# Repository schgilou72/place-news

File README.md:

# place-news

KiCad action plugins for boards where **isolation matters** (switch-mode power
supplies, mains and high-voltage circuits):

- **place-news** — automatic component placement (simulated annealing) that
  keeps parts as far apart as your clearance and creepage rules demand, and
  honours KiCad rule areas (keep-outs, placement areas). Then a tidy-up: parts
  in rows and columns, readable references, and an untangled ratsnest (fewer
  vias).
- **place-news — Route (Freerouting)** — autorouting with
  [Freerouting](https://github.com/freerouting/freerouting), with your net-class
  clearances and custom `.kicad_dru` rules (clearance, creepage) passed to the
  router; fewer vias, a try on the two outer layers when the board has more,
  and a ground plane on the top layer that keeps the creepage distances.
- **place-news — Aesthetic check** — scores the look and the cost of the
  placement and routing, marks every issue on the board and in a visual
  report, estimates how many layers the board needs, and learns your taste
  from your opinion and from your own corrections.
- **place-news — Sourcing (BOM)** — stock, prices, minimum orders, lifecycle
  and replacements of every BOM line at DigiKey, Mouser, Farnell, TME and
  LCSC; the chosen parts written into the components' fields, a BOM with the
  designators, unit prices and minimum orders, and one order list per
  distributor.

KiCad's own DRC stays the judge: placement and routing can finish with a DRC run, and the
rules are always applied on the safe side (straight-line distance, never longer
than KiCad's creepage path).

place-news is derived from [CadMust-Neo](https://github.com/remiblokker/CadMust-Neo)
by Remi Blokker (MIT licence).

## Requirements

- KiCad 10.0 (tested with 10.0.6). Uses the SWIG Python API, which KiCad 10
  still ships (it is planned to be removed in KiCad 11).
- For routing: **Java 25 or later** and **Freerouting 2.4 or later**
  (`freerouting-2.x.x-executable.jar`, from the
  [Freerouting releases](https://github.com/freerouting/freerouting/releases)
  or installed by KiCad's Freerouting plugin). Java: e.g.
  [Eclipse Temurin](https://adoptium.net/temurin/releases/).
- For sourcing: an internet connection, and the free API keys of the
  distributors you use (LCSC needs none).
- Nothing else: pure Python, no extra packages.

## Installation

Download the archive from the
[Releases](https://github.com/schgilou72/place-news/releases) page.

**Plugin and Content Manager (recommended):** in KiCad, *Plugin and Content
Manager → Install from File…* and choose `place-news-<version>-pcm.zip`.

**Manual:** in the PCB editor, *Tools → External Plugins → Open Plugin
Directory*, unzip `place-news-<version>-plugin.zip` there (it holds the
`place_news/` folder), then *Tools → External Plugins → Refresh Plugins*.

Four toolbar buttons appear: placement (green grid), routing (trace with a
dashed isolation line), the aesthetic check (magnifier) and sourcing (cart).

To try it: open `examples/flyback/flyback.kicad_pcb` (an isolated flyback
with HV / PRI / SEC net classes and 6 mm creepage rules, parts still piled up)
and run the placement and the routing.

## Placement

1. Draw the board outline on Edge.Cuts; lock connectors, mounting holes and
   anything mechanically fixed.
2. Optional: rule areas with *Keep out footprints / pads* reserve space; rule
   areas with *Placement* enabled (sheet, component class or group) keep their
   parts inside — and, with *Exclusive placement areas*, other parts outside.
3. Click **place-news**, choose a preset, **Optimize**.
4. The result dialog lists wirelength, overlaps, isolation, placement areas,
   keep-outs, alignment, ratsnest crossings and silkscreen. *Reject* (or
   *Edit → Undo*) restores the previous placement.

### Tidy layout

- **Rows and columns** (*Align parts of the same type in rows / columns*, on by
  default): parts with the same footprint and orientation that sit roughly in
  a row or a column are put on one line through their centres, and lines of
  three or more are evenly spaced. A locked part of the same type serves as
  the anchor. A move is kept only if no rule gets worse (overlap, isolation,
  keep-outs, placement areas, board edge) and the wirelength grows by 3 % at
  most.
- **Readable references**: each reference is centred on its part, horizontal
  or vertical reading bottom to top (never upside down nor top to bottom),
  along the long side of the part. It never touches a pad or another
  reference: when pads take the centre, it goes beside the part, centred on
  its axis. References of locked parts are left alone.
- **Untangled ratsnest** (*Reduce cost: untangle the ratsnest*, on by
  default): every crossing of two ratsnest lines tends to cost a via. Identical
  parts swap places with their nearest twins and two-pad parts turn round
  (180°) when that removes crossings; rows, columns and orientation axes stay.
  Power nets are left out (they go to a plane or a pour). Same safeguards as
  above, 2 % of wirelength at most. On KiCad's demo boards, with their
  hand-made placements: complex_hierarchy 28 → 18 crossings, pic_programmer
  22 → 17.

### Isolation during placement

For every pair of pads on different nets, the required distance is the larger
of:

- the clearance KiCad applies: net-class clearance (the larger of the two), or
  the last matching custom `clearance` rule, never below the board minimum;
- `physical_clearance` rules;
- `creepage` rules. KiCad evaluates creepage **between nets** (with a stand-in
  track of each net on every copper layer), so creepage conditions can use net
  names, net classes and layers, not footprint properties.

Non-plated holes (mounting holes) count for creepage only. Pairs inside one
footprint cannot be fixed by placement; they are reported separately ("inside
footprints"), as are pairs between two locked parts.

### Supported rule conditions

`A.`/`B.` with `NetClass`, `NetName`, `Type`, `Pad_Type`, `Layer`,
`hasNetclass()`, `hasExactNetclass()`, `hasComponentClass()`,
`memberOfSheet()`, `memberOfSheetOrChildren()`, `memberOfFootprint()`
(reference, `lib:footprint` or `${Class:…}`), `memberOfGroup()`,
`existsOnLayer()`, `isPlated()`, combined with `!`, `&&`, `||`, `==`, `!=` and
parentheses. Semantics follow KiCad: last matching rule wins, a rule matches if
its condition holds for (A, B) or (B, A), `&&` binds less tightly than `||`,
string `==` is case-insensitive and accepts `*`/`?` in a right-hand literal.
A rule using anything else is listed as ignored in the dialogs — never guessed.

Example (`<project>.kicad_dru`):

```
(version 1)
(rule "isolation creepage"
  (constraint creepage (min 6mm))
  (condition "(A.hasNetclass('HV') || A.hasNetclass('PRI')) && B.hasNetclass('SEC')"))
(rule "isolation clearance"
  (constraint clearance (min 4mm))
  (condition "(A.hasNetclass('HV') || A.hasNetclass('PRI')) && B.hasNetclass('SEC')"))
```

## Routing with Freerouting

1. Place the parts (with place-news or by hand) and save the board.
2. Click **place-news — Route (Freerouting)**. The dialog finds the
   Freerouting jar and Java (or lets you pick them) and shows the isolation
   distances that will be given to the router.
3. Cost options: **Fewer vias** (Freerouting's via cost × 3; if that leaves
   connections unrouted, the board is routed again at the usual cost and the
   more complete result is kept) and, on boards with more than two copper
   layers, **Try the 2 outer layers first** (the inner layers become planes
   for Freerouting; if every connection is made, that result is kept and the
   summary says the inner layers can go, unless they are planes).
4. **Ground plane**: *Pour on the top layer (F.Cu)*, with the ground net
   (GND, PGND, 0V… found by name). See below.
5. **Route**. Freerouting runs in the background (progress, *Cancel*), the
   routes are imported, the pour is made, then KiCad's DRC runs on a copy of
   the board and the summary shows unrouted connections, vias, the routing
   room, the pour and the clearance / creepage results.
6. *Edit → Undo* reverts the routing and the pour.

What place-news changes in the Specctra file before routing:

- **Rule areas**: KiCad exports every rule area as a full routing keep-out,
  even areas that only keep out footprints or pads, and placement areas. Each
  area now follows its own *Keep out tracks / vias* settings.
- **Isolation rules**: Freerouting knows one clearance per pair of net
  classes. Each class gets the clearance its own nets need between them, and a
  `class_class` rule is written for every pair of classes that needs another
  value (e.g. 6 mm between primary and secondary classes). Creepage becomes a
  straight-line clearance.
- KiCad's `smd_smd` pad-to-pad allowance is dropped when it would let the
  default class bypass these rules; Freerouting may then report pad-to-pad
  "violations" inside fine-pitch footprints (pads are fixed; KiCad's DRC is
  what counts).
- Freerouting ≥ 2.4 may fan out SMD pins with the default class's vias when a
  class's own via does not fit; that is disabled, since those vias would carry
  the default clearance.
- Parts never move: the session's placement section is ignored on import.

Freerouting runs with `--usage_and_diagnostic_data.disable_analytics=true`.
It still checks GitHub for a newer version when it starts.

### Ground plane on the top layer

The chosen net is poured over the whole top layer (zones named
`place-news pour`; running again replaces them). KiCad's zone filler keeps
the clearances, but not the creepage distances — and a pour runs along the
board surface, the very path creepage is measured on. So every copper item on
the top layer whose required distance to the pour's net (clearance, physical
clearance or creepage, from the net classes and the custom rules) is larger
than the plain clearance is kept clear by that distance (+ 20 µm for the
fill's rounding). Each cluster of such items — a primary side, say — gets one
convex cut-out: a clean isolation boundary, no copper fingers between the
primary parts. Islands are removed; pads connect with thermal reliefs. On the
example flyback, KiCad's DRC finds no clearance, creepage or unconnected item
with the pour.

### Known KiCad behaviour

KiCad's creepage check treats rule areas as items without a net: with a rule
such as `A.hasNetclass('HV') && !B.hasNetclass('HV')`, it reports "creepage"
between HV pads and nearby rule-area outlines. Writing the rule against an
explicit class (`B.hasNetclass('SEC')`) avoids it. The route summary counts
these separately.

## Aesthetic check

**place-news — Aesthetic check** scores the board out of 100 in three groups
and numbers every issue on the *User.Comments* layer (one group, easy to
delete) and in an HTML report next to the board (`<board>-aesthetic-check.html`:
drawing of the board, markers, criteria, issues; hover a row to find its
marker).

- **Placement**: same-type parts aligned, one orientation per part type,
  references readable (0° / 90°), on their part or its axis, clear of pads.
- **Routing**: 45° steps, no acute angles, no small zigzags, no long detours
  (routed length against the shortest 45° tree), tracks leaving pads straight.
- **Cost**: few vias, untangled ratsnest, few drill sizes, no drill under
  0.3 mm, no track under 0.15 mm, parts on one side, no empty inner layer,
  layer count fitting the routing room, board not larger than needed.

**Learning.** The dialog asks what you think (👍 / 👎, and optionally what
bothers you most): the criteria you name gain weight. When you edit a board
place-news produced and run the check again, the criteria your edits improved
gain weight, those you let degrade lose some, and the knobs place-news turned
(tidy-up budgets, via cost) are rewarded or penalised by how much you had to
fix — a small evolution-strategies loop: each run tries the knobs a little
differently and keeps what you liked. Everything stays in
`place-news/place-news-aesthetics.json` in KiCad's settings folder.

### How many layers?

The routing room per net — the rule of thumb

    (board area × routing layers − parts area) / number of nets

— is compared with what an average net needs: its ratsnest length (45°
spanning tree, × 1.3 for detours) times its track pitch (net-class width +
clearance), over the share of free area tracks can really use (60 %). That is
Coors' "wiring demand / routing capacity per layer". Parts with pads in a grid
(BGA) also need layers to escape: rings of pads ÷ (tracks between pads + 1).
Inner layers used as planes are not routing room, and never a cost (power,
EMC). Fewer layers are suggested only with 30 % of room to spare.

Calibrated on the boards shipped with KiCad: the estimated track area matches
the routed one within about 10 %. Quick rules of thumb are shown next to it
for comparison; they ask for far too many layers on fine-pitch SMD boards:

| Board | Layers | Pin density (in² per 14 pins) | Parts / board | Pins per cm² | place-news |
|---|---|---|---|---|---|
| pic_programmer (through-hole) | 2 | 1.46 → 2 | 49 % | 1.5 | 2 fit |
| interf_u | 2 | 0.71 → 2 + planes | 52 % | 3.1 | 2 fit |
| sonde xilinx | 2 | 0.70 → 2 + planes | 80 % → "6–8" | 3.1 | 2 fit |
| StickHub (fine-pitch SMD) | 2 | 0.05 → 10 signal | 152 % → "6–8" | 45 → "4+" | 2 just fit |
| video | 2 + 2 planes | 0.30 → 8 signal | 74 % → "6–8" | 7.3 | 2 fit |
| vme-wren (FPGA BGA) | 12 | 0.11 → 10 signal | 63 % | 19 | 8 routing (BGA escape) |

## Sourcing (BOM)

**place-news — Sourcing (BOM)** asks the distributors, for every line of the
bill of materials, for the stock, the price breaks, the minimum order and the
multiple, the lifecycle (active, NRND, end of life, obsolete) and the
replacements; then it writes the chosen parts into the components and saves a
BOM and one order list per distributor.

### Keys

Each distributor has a free API for its catalogue. Create your own keys once
and enter them in the dialog; the *Test* button next to each one tells at once
whether it works.

| Distributor | What to create (free) | Where |
|---|---|---|
| DigiKey | an app with *Product Information v4*, client credentials: client ID and secret | [developer.digikey.com](https://developer.digikey.com) |
| Mouser | a *Search API* key | [mouser.com/api-hub](https://www.mouser.com/api-hub/) |
| Farnell / element14 | a *Product Search API* key (store: `fr.farnell.com` by default) | [partner.element14.com](https://partner.element14.com) |
| TME (beta) | an API v2 application: token and secret | [developers.tme.eu](https://developers.tme.eu) |
| LCSC | nothing: JLCPCB / LCSC public catalogue | — |

The keys stay in your KiCad settings folder (`place-news/sourcing.json`,
readable by you only) and only go to the distributor they belong to. Answers
are kept one day (`place-news/sourcing-cache.json`): running again is quick
and spares the daily quotas (Mouser: 1000 calls a day, 30 a minute — place-news
paces its calls).

### What is searched

Footprints with the same value, footprint, MPN, manufacturer and ratings
fields (Voltage, Tolerance, Power, Dielectric…) make one BOM line. DNP parts,
parts excluded from the BOM, mounting holes and fiducials are left out (and
listed in the report). For each line:

- **with an MPN field** (`MPN`, `Manufacturer_Part_Number`, `MFR_PN`, KiCost's
  `manf#`… any usual spelling): that part at every distributor;
- **with a distributor part number** (fields `DigiKey`, `Mouser`, `Farnell`,
  `TME`, `LCSC`, e.g. `LCSC = C25804`): that part, then its MPN at the others;
- **no MPN, but a value that is a part name** (`IRF840`, `UC3843BD1R2G`):
  searched as a part number;
- **no MPN, a resistor, capacitor or inductor**: searched by value, package
  and ratings. Only parts that fit are *proposed*: same package (read from the
  footprint: chip size, SOT / TO / SOIC with their pin count and isolated
  tab, radial diameter and pitch, axial length, …), same value, voltage,
  current and power at least as high, tolerance at most as wide, dielectric
  as good (C0G > X7R > X5R), safety class as good (Y1 > Y2 > X1 > X2). Without a
  tolerance in the schematic, resistors are 1 % and chip capacitors X5R or
  better (settings). A package or a rating that cannot be read is not
  accepted: a proposal is never a guess — give an MPN for such parts;
- any other part without a part number is reported "not found: needs a part
  number".

The package is checked for parts found by part number too: one MPN can be
sold in several package variants (LCSC lists PC817C in DIP-4 and in SMD-4P),
so the variant that fits the footprint is bought, and a part whose package
does not fit is flagged *check package*. Same pin count is not enough where
it does not fix the size: QFN / DFN / QFP bodies (QFN-32 5×5 or 7×7) and DIP
row spacings (300 or 600 mil) are compared when both sides give them.

### What is bought

- **Quantity**: per board × number of boards + spare parts (10 % by default,
  rounded up), then raised to the **minimum order**, rounded to the
  **multiple** (reels, cut tape) and priced at the **price break** reached.
  Lines buying the same part share one order (one minimum, one multiple).
- **Where**: the first distributor of *your list* (drag to reorder, untick to
  skip) that has the stock for the quantity actually bought — or, as an
  option, wherever the line total is the lowest. Never an obsolete part when
  there is another.
- **No surprise**: each line shows the unit price, the minimum order and the
  multiple, the line total, and the money spent beyond the need because of
  minimum orders; the totals are per distributor and per board. Prices are
  dated, in euros, excluding VAT and shipping; prices in another currency
  (LCSC: US dollars) are converted at the ECB rate of the day.
- **Replacements**: when a part is short, at the end of its life or not
  found, the distributors' own suggestions (DigiKey substitutes, Mouser
  suggested replacement, TME similar products, LCSC alternatives) and a
  search by parameters at every distributor give replacements with the same
  package and the ratings kept, in stock for the quantity bought.

The results dialog colours each line by status (OK, short stock, end of life,
proposed, not found, check package). Select a line to see every offer,
proposal and replacement; double-click one to use it.

### What you get

- **Write into the components**: fields `MPN`, `Manufacturer`, the part
  number at each distributor that carries the part (`DigiKey`, `Mouser`,
  `Farnell`, `TME`, `LCSC`) and the key parameters (`Voltage`, `Current`,
  `Power`, `Tolerance`, `Dielectric`, `Safety class` — only where the field is
  empty: your figures are kept). New fields are hidden, on the fabrication
  layer. To bring them into the schematic: *Tools → Update Schematic from
  PCB*, tick *Other fields*. *Edit → Undo* removes them from the board.
- **Save the BOM and the order lists**, next to the board:
  - `<board>-bom.csv` — designators, quantity per board / needed / ordered,
    value, package, footprint, manufacturer, MPN, distributor and part
    number, unit price, minimum order, multiple, line total, extra due to the
    minimum order, stock, lifecycle, lead time, status, replacements, link
    (`;` and decimal commas: opens as is in a French Excel);
  - `<board>-order-<distributor>.csv` — part number, quantity, customer
    reference (the designators; DigiKey and Mouser print it on each bag's
    label), MPN, manufacturer, unit price, minimum, multiple, total: upload it
    in the distributor's BOM / list tool (map the columns once);
  - `<board>-sourcing.html` — the report: totals, statuses and every line with
    its choices.

Tried live with LCSC; DigiKey, Mouser, Farnell and TME are tested on answers
shaped like their documented APIs — use the *Test* buttons with your keys.
TME's API v2 is new: its support is marked beta.

## Tips

- Give the high-voltage and the isolated sides their own net classes (e.g. HV,
  PRI, SEC) and write isolation rules between classes.
- Parts that bridge the barrier (transformers, optocouplers, Y capacitors) must
  have pin spacing at least the creepage distance; otherwise their pins are
  reported "inside footprints" and the router cannot leave those pins legally.
- "Move selected only" reworks one area without touching the rest.
- Power nets (GND, VCC, …) are excluded from wirelength; adjust the list in
  Normal / Expert mode.

## Tests

```bash
python3 -m unittest tests.test_optimizer tests.test_rules_isolation tests.test_routing \
  tests.test_aesthetics tests.test_cost tests.test_sourcing -v
```

These need no KiCad and no network (the distributors' answers are canned). With KiCad's Python (`pcbnew`, `kicad-cli`) the
end-to-end tests build an isolated flyback board, place it, check it with
KiCad's DRC, route it through Freerouting, pour GND on the top layer and check
again, and try the outer layers of a 4-layer version:

```bash
PLACE_NEWS_FREEROUTING_JAR=/path/to/freerouting-2.4.1-executable.jar \
  python3 -m unittest tests.e2e_kicad -v
xvfb-run -a python3 tests/gui_smoke.py          # placement action, dialogs included
xvfb-run -a python3 tests/gui_route_smoke.py    # routing action, dialogs included
xvfb-run -a python3 tests/gui_check_smoke.py    # aesthetic check and learning
xvfb-run -a python3 tests/gui_sourcing_smoke.py # sourcing with LCSC (network)
```

(The GUI scripts need the Python that KiCad's wxPython was built for.)

## Licence

[MIT](LICENSE). Freerouting is a separate program (GPL-3.0), not included.

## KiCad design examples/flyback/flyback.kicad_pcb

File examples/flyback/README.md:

# Example: isolated flyback

A small isolated flyback converter as it looks right after *Update PCB from
Schematic*: every part piled up in the middle of a 100 x 60 mm board.

- Net classes: **HV** (rectified bus, switch node: 0.6 mm), **PRI** (primary
  control: 0.25 mm), **SEC** (secondary: 0.2 mm).
- `flyback.kicad_dru`: 6 mm creepage and 4 mm clearance between the primary
  side (HV, PRI) and the secondary side (SEC).
- A placement area keeps the `/Secondary/` sheet on the right; rule areas
  keep footprints / pads out of a corner and of two back-side regions.

Open `flyback.kicad_pcb` in KiCad 10, run **place-news**, then
**place-news — Route (Freerouting)**, then the DRC.

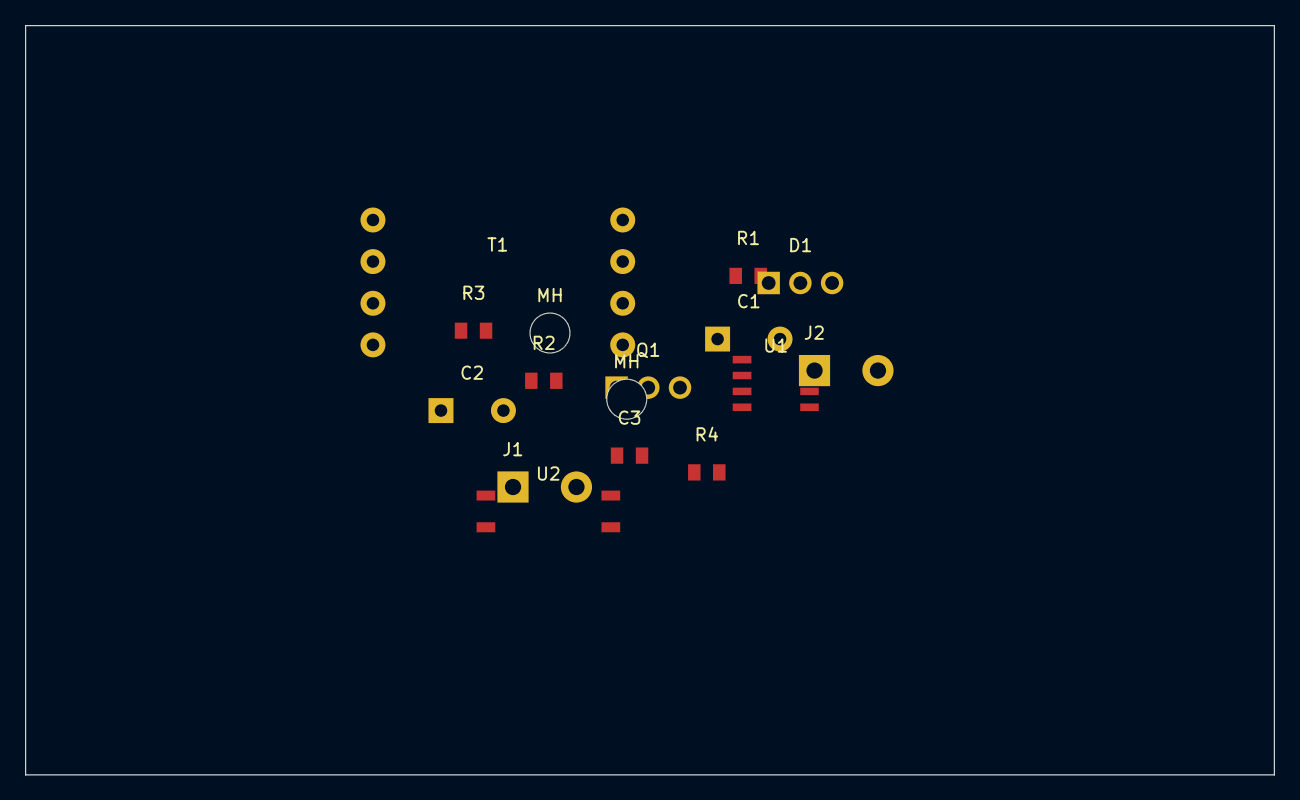
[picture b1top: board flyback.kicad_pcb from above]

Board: 2 copper layers, 100.0 x 60.0 mm, 16 parts (0 on the bottom side), 13 nets, no tracks yet.

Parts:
C1, C2: CAP_D10
C3: R0805
D1: TO220
J1, J2: TB2
MH: MH3
MH#2: MH3
Q1: TO220
R1, R2, R3, R4: R0805
T1: XFMR
U1: SOIC8
U2: OPTO4W

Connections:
FB_P: U1.2, U2.1
FB_S: R2.2, R3.1, U2.4
GATE: Q1.1, R1.2
GATE_DRV: R1.1, U1.1
GND: C2.2, J2.2, R3.2, U2.3
HV_BUS+: C1.1, J1.1, T1.1
HV_BUS-: C1.2, C3.2, J1.2, R4.2, U1.4, U2.2
PRI_RTN: Q1.3, R4.1
PRI_VCC: C3.1, U1.3
SEC_A: D1.1, T1.5
SEC_B: D1.3, T1.6
SW: Q1.2, T1.2
VOUT: C2.1, D1.2, J2.1, R2.1
